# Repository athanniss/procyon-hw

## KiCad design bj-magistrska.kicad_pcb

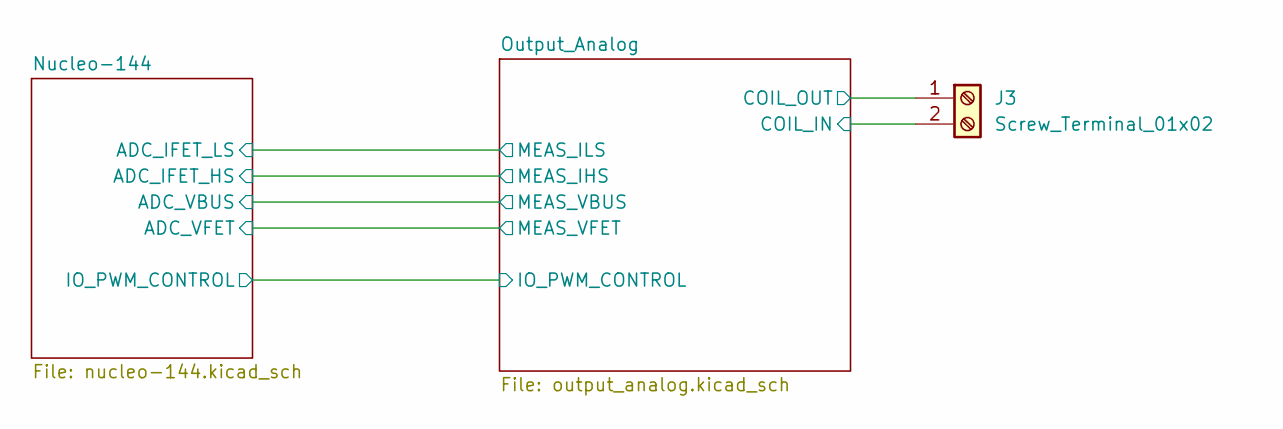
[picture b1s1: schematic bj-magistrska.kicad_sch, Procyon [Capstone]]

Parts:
J3: Screw_Terminal_01x02; TerminalBlock_Phoenix_MKDS-1,5-2-5.08_1x02_P5.08mm_Horizont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; Mfg. Part Number 1985904

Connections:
/Output_Analog/COIL_IN: J3.2; also elsewhere on the board
/Output_Analog/COIL_OUT: J3.1; also elsewhere on the board

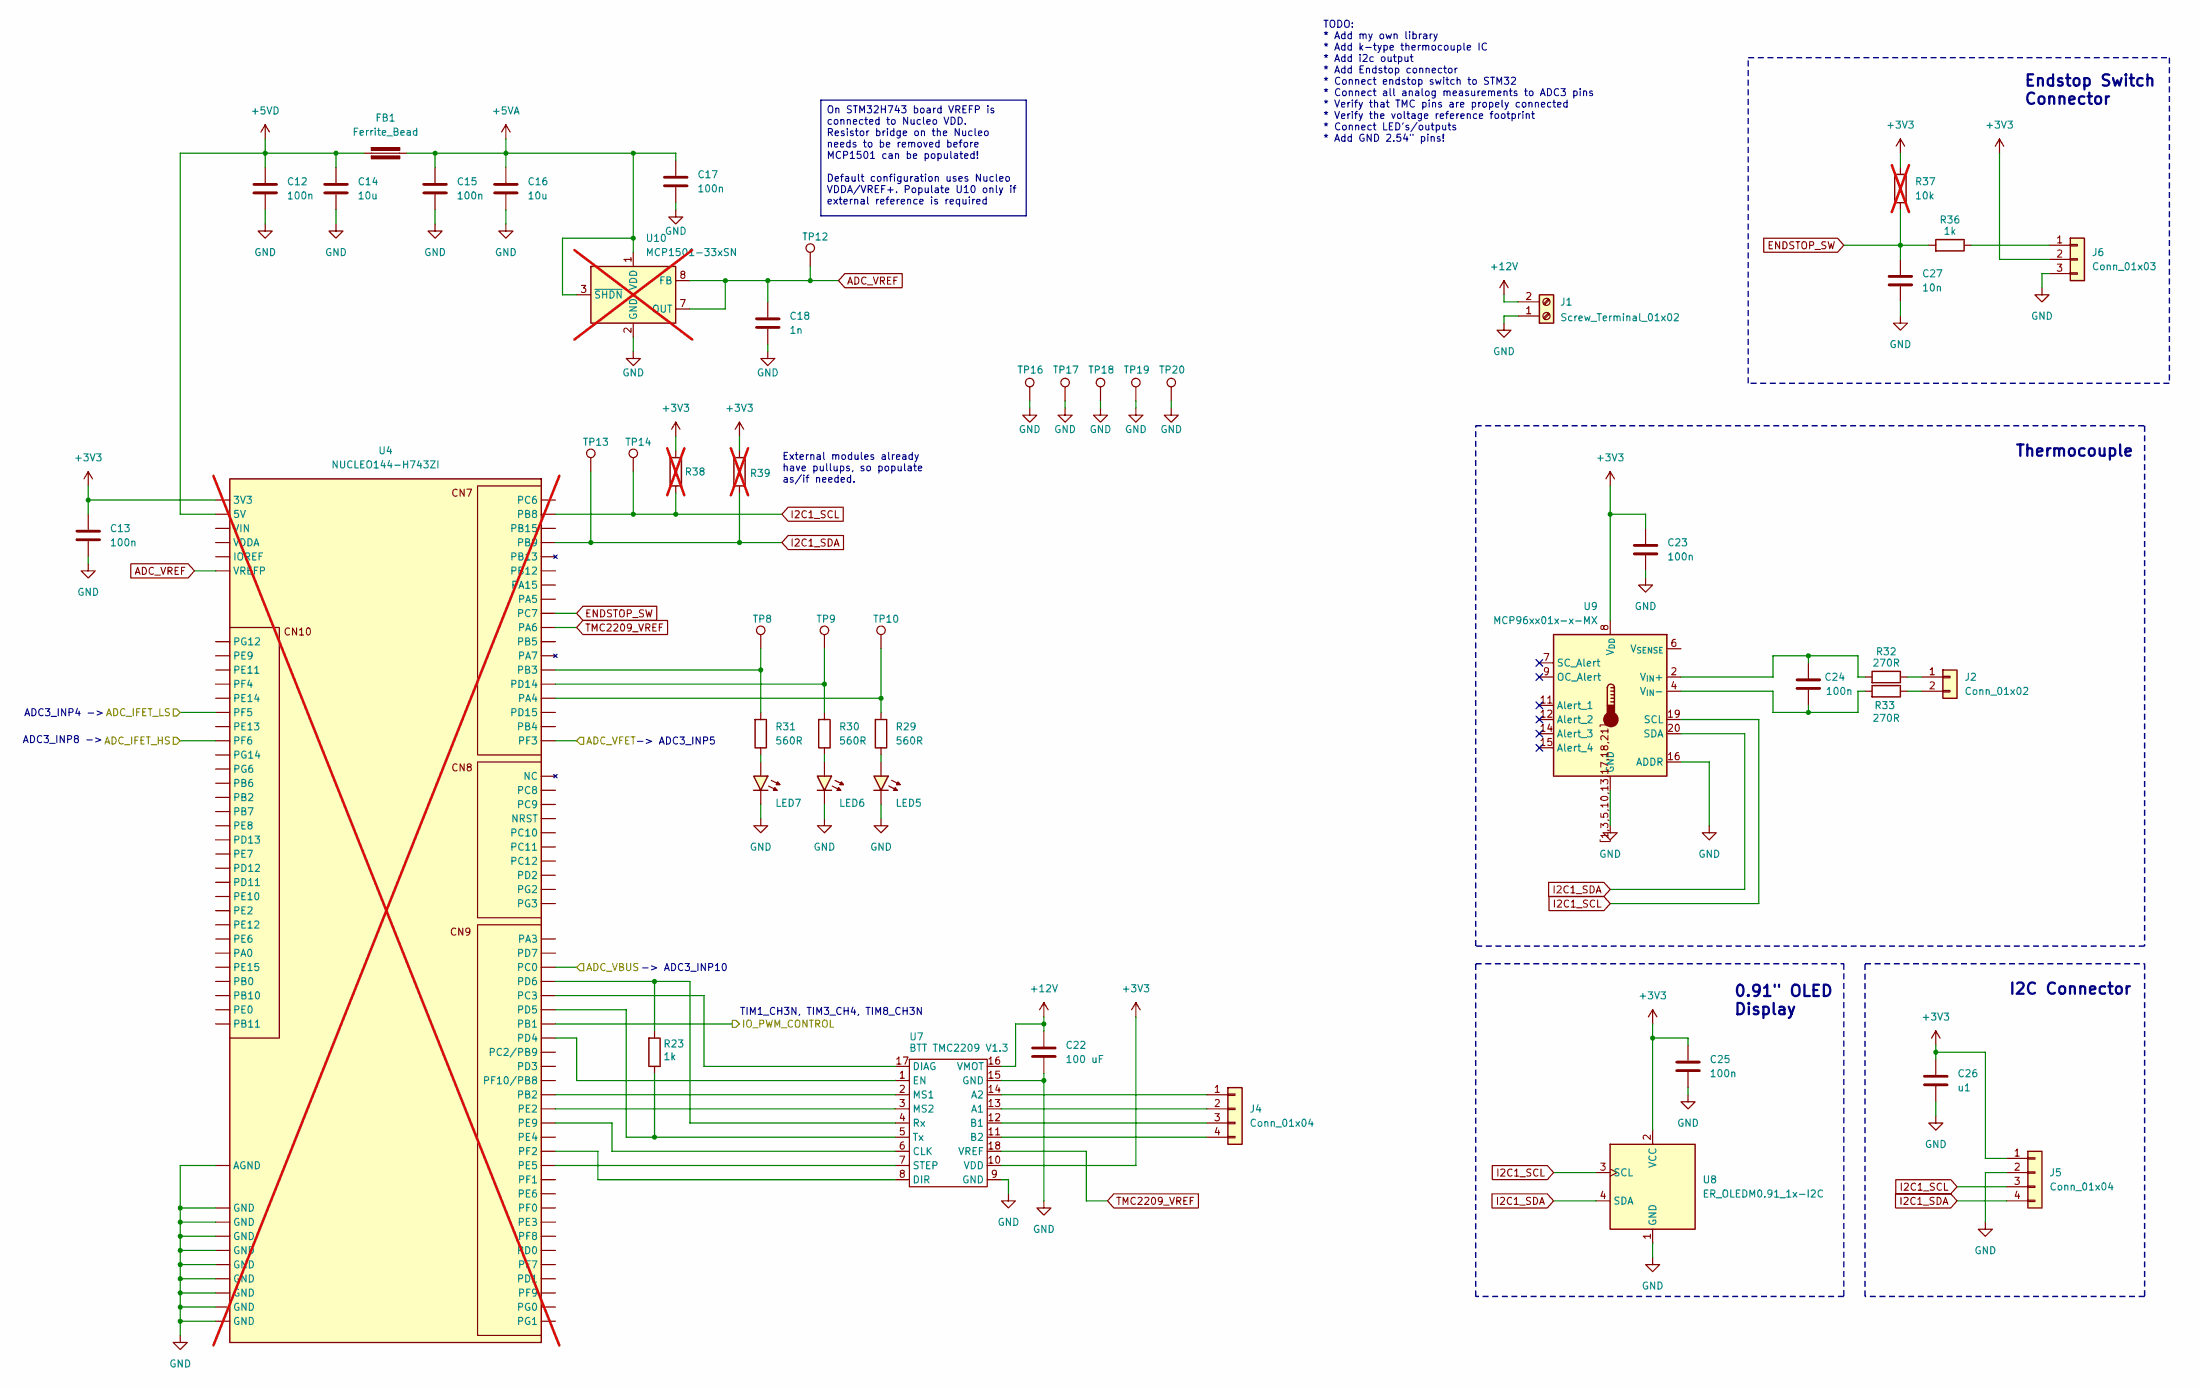
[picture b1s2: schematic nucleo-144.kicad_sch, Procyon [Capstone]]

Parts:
C12, C13, C15, C17, C23, C24, C25: 100n; C_0603_1608Metric
C14, C16: 10u; C_0805_2012Metric
C18: 1n; C_0603_1608Metric
C22: 100 uF; C_Elec_6.3x5.8
C26: u1; C_0603_1608Metric
C27: 10n; C_0603_1608Metric
FB1: Ferrite_Bead; Ferrite_0603_1608Metric
J1: Screw_Terminal_01x02; TerminalBlock_Phoenix_MKDS-1,5-2-5.08_1x02_P5.08mm_Horizont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; Mfg. Part Number 1985904
J2: Conn_01x02; JST_PH_S2B-PH-K_1x02_P2.00mm_Horizontal
J4, J5: Conn_01x04; JST_PH_S4B-PH-K_1x04_P2.00mm_Horizontal
J6: Conn_01x03; JST_PH_S3B-PH-K_1x03_P2.00mm_Horizontal
LED5, LED6, LED7: ORANGE; LED_0805_2012Metric
R23, R36: 1k; R_0603_1608Metric
R29, R30, R31: 560R; R_0603_1608Metric
R32, R33: 270R; R_0603_1608Metric
R37: 10k; R_0603_1608Metric; not fitted
R38, R39: R_0603_1608Metric; not fitted
TP8, TP9, TP10, TP16, TP17, TP18, TP19, TP20: TestPoint; PinHeader_1x01_P2.54mm_Vertical
TP12, TP13, TP14: TestPoint; PinHeader_1x01_P2.00mm_Vertical
U4: NUCLEO144-H743ZI; ST_Zio_Only_Connectors_144_STLink; not fitted
U7: BTT TMC2209 V1.3; BTT-TMC2209-V1.3_RAISED
U8: ER_OLEDM0.91_1x-I2C
U9: MCP96xx01x-x-MX; QFN-20-1EP_5x5mm_P0.65mm_EP3.35x3.35mm
U10: MCP1501-33xSN; SOIC-8_3.9x4.9mm_P1.27mm; not fitted

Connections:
+3V3: C13.1, C23.1, C25.1, C26.1, J5.1, J6.2, R37.1, R38.1, R39.1, U4.CN8_7 (3V3), U7.10 (VDD), U8.2 (VCC), U9.8 (V_{DD})
+5VA: C15.1, C16.1, C17.1, FB1.2, U10.1 (VDD), U10.3 (~SHDN); also elsewhere on the board
+5VD: C12.1, C14.1, FB1.1, U4.CN8_9 (5V); also elsewhere on the board
+12V: C22.1, J1.2, U7.16 (VMOT); also elsewhere on the board
/Nucleo-144/ADC_IFET_HS: U4.CN10_11 (PF6); also elsewhere on the board
/Nucleo-144/ADC_IFET_LS: U4.CN10_9 (PF5); also elsewhere on the board
/Nucleo-144/ADC_VBUS: U4.CN9_3 (PC0); also elsewhere on the board
/Nucleo-144/ADC_VFET: U4.CN7_20 (PF3); also elsewhere on the board
/Nucleo-144/IO_PWM_CONTROL: U4.CN9_7 (РВ1); also elsewhere on the board
ADC_VREF: C18.1, TP12.1 (1_1), U4.CN7_6 (VREFP), U10.7 (OUT), U10.8 (FB)
ENDSTOP_SW: C27.1, R36.1, R37.2, U4.CN7_11 (PC7)
GND: C12.2, C13.2, C14.2, C15.2, C16.2, C17.2, C18.2, C22.2, C23.2, C25.2, C26.2, C27.2, J1.1, J5.2, J6.3, LED5.1 (K), LED6.1 (K), LED7.1 (K), TP16.1 (1_1), TP17.1 (1_1), TP18.1 (1_1), TP19.1 (1_1), TP20.1 (1_1), U4.CN7_8 (GND), U4.CN8_11 (GND), U4.CN8_13 (GND), U4.CN9_12 (GND), U4.CN9_23 (GND), U4.CN10_3 (AGND), U4.CN10_5 (GND), U4.CN10_17 (GND), U4.CN10_22 (GND), U4.CN10_27 (GND), U7.9 (GND), U7.15 (GND), U8.1 (GND), U9.1 (GND), U9.3 (GND), U9.5 (GND), U9.10 (GND), U9.13 (GND), U9.16 (ADDR), U9.17 (GND), U9.18 (GND), U9.21 (GND), U9.[1,3,5,10,13,17,18,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 (GND), U10.2 (GND), U10.4 (GND), U10.5 (GND), U10.6 (GND); also elsewhere on the board
I2C1_SCL: J5.3, R38.2, TP14.1 (1_1), U4.CN7_2 (PB8), U8.3 (SCL), U9.19 (SCL)
I2C1_SDA: J5.4, R39.2, TP13.1 (1_1), U4.CN7_4 (PB9), U8.4 (SDA), U9.20 (SDA)
unnamed: J2.1, R32.2
unnamed: J2.2, R33.2
unnamed: J4.1, U7.14 (A2)
unnamed: J4.2, U7.13 (A1)
unnamed: J4.3, U7.12 (B1)
unnamed: J4.4, U7.11 (B2)
unnamed: J6.1, R36.2
unnamed: LED5.2 (A), R29.2
unnamed: LED6.2 (A), R30.2
unnamed: LED7.2 (A), R31.2
unnamed: R29.1, TP10.1 (1_1), U4.CN7_17 (PA4)
unnamed: R31.1, TP8.1 (1_1), U4.CN7_15 (PB3)
unnamed: U4.CN9_8 (PD4), U7.1 (EN)
unnamed: R23.2, U4.CN9_6 (PD5), U7.5 (Tx)
unnamed: R23.1, U4.CN9_4 (PD6), U7.4 (Rx)
unnamed: R30.1, TP9.1 (1_1), U4.CN7_16 (PD14)
unnamed: U4.CN9_14 (PE2), U7.3 (MS2)
unnamed: U4.CN9_17 (PF2), U7.8 (DIR)
unnamed: U4.CN9_18 (РЕ5), U7.7 (STEP)
unnamed: U4.CN9_15 (РЕ9), U7.6 (CLK)
unnamed: U4.CN9_5 (РСЗ), U7.17 (DIAG)
unnamed: U4.CN9_13 (РВ2), U7.2 (MS1)
unnamed: C24.1, R32.1, U9.2 (V_{IN}+)
unnamed: C24.2, R33.1, U9.4 (V_{IN}-)
TMC2209_VREF: U4.CN7_12 (PA6), U7.18 (VREF)

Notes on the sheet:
TIM1_CH3N, TIM3_CH4, TIM8_CH3N
Thermocouple
0.91" OLED Display
ADC3_INP4 ->
Endstop Switch Connector
ADC3_INP8 ->
External modules already have pullups, so populate as/if needed.
TODO: * Add my own library * Add k-type thermocouple IC * Add i2c output * Add Endstop connector * Connect endstop switch to STM32 * Connect all analog measurements to ADC3 pins * Verify that TMC pins are propely connected * Verify the voltage reference footprint * Connect LED's/outputs * Add GND 2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
-> ADC3_INP10
-> ADC3_INP5
I2C Connector
On STM32H743 board VREFP is connected to Nucleo VDD. Resistor bridge on the Nucleo needs to be removed before MCP1501 can be populated! Default configuration uses Nucleo VDDA/VREF+. Populate U10 only if external reference is required

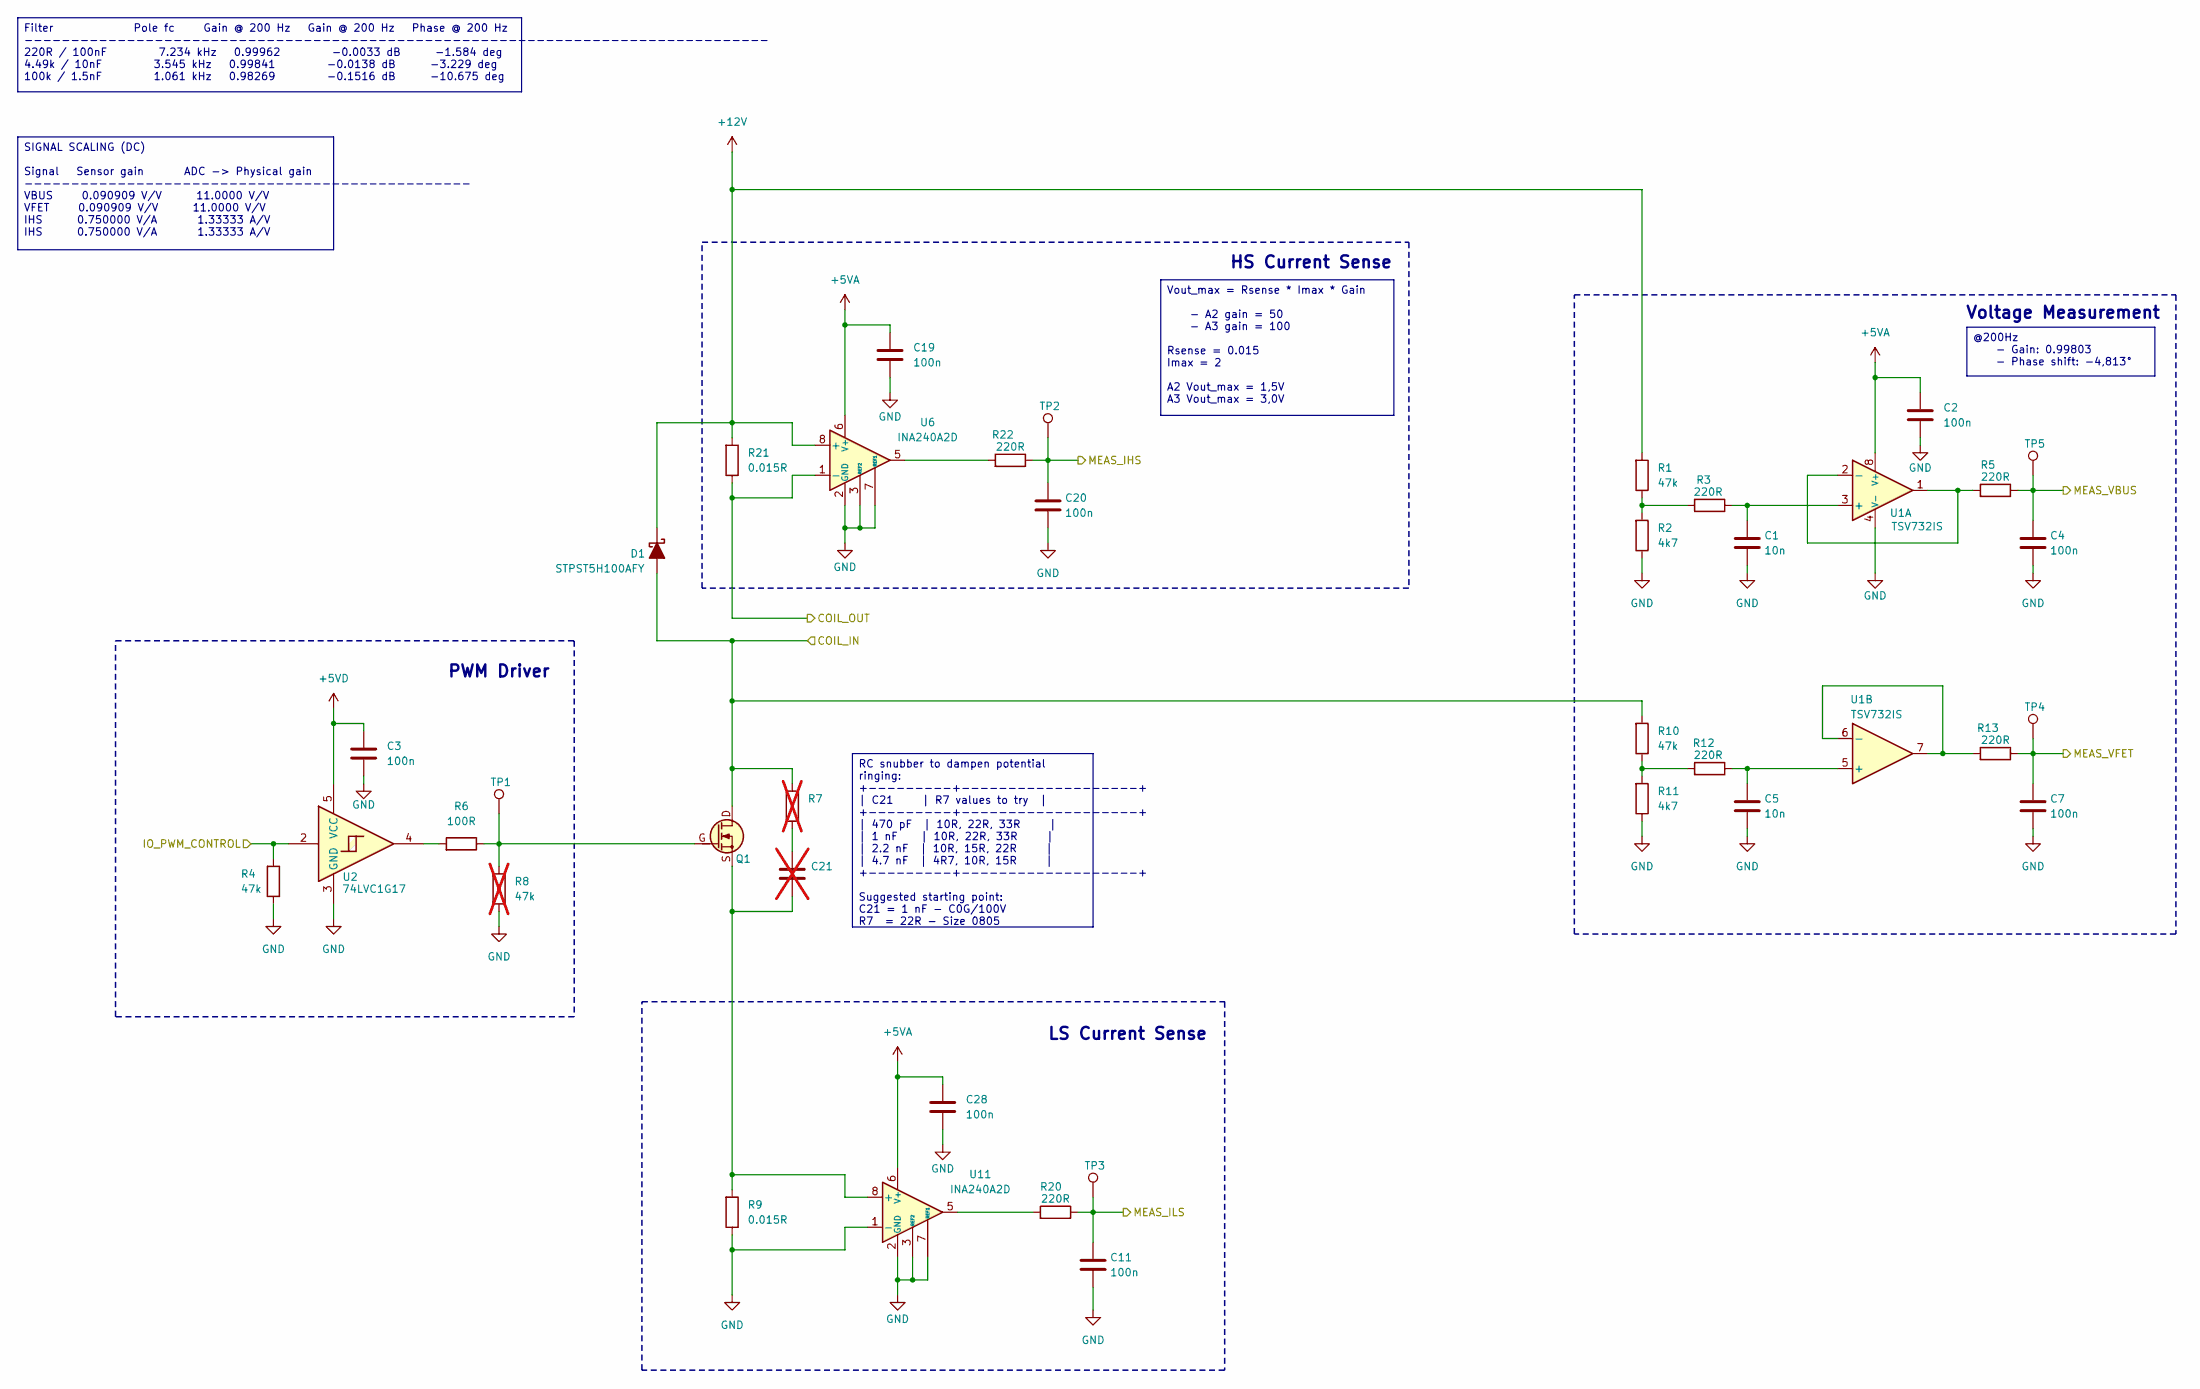
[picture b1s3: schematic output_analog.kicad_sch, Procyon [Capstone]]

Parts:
C1, C5: 10n; C_0603_1608Metric
C2, C3, C4, C7, C11, C19, C20, C28: 100n; C_0603_1608Metric
C21: C_0603_1608Metric; not fitted
D1: STPST5H100AFY; D_SOD-128; Mfg. Part Number STPST5H100AFY
Q1: DMTH10H009LPSQ-13; Diodes_PowerDI5060-8_ThermalVias; Mfg. Part Number DMTH10H009LPSQ-13
R1, R4, R10: 47k; R_0603_1608Metric
R2, R11: 4k7; R_0603_1608Metric
R3, R5, R12, R13, R20, R22: 220R; R_0603_1608Metric
R6: 100R; R_0603_1608Metric
R7: R_0805_2012Metric; not fitted
R8: 47k; R_0603_1608Metric; not fitted
R9, R21: 0.015R; R_1206_3216Metric; Mfg. Part Number MFSA1206R0150FCM
TP1, TP2, TP3, TP4, TP5: TestPoint; PinHeader_1x01_P2.00mm_Vertical
U1: TSV732IS; MSOP-8_3x3mm_P0.65mm; Mfg. Part Number TSV732IST
U2: 74LVC1G17; SOT-23-5; Mfg. Part Number SN74LVC1G17DBVR
U6, U11: INA240A2D; SOIC-8_3.9x4.9mm_P1.27mm

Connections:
+5VA: C2.1, C19.1, C28.1, U1.8 (V+), U6.6 (V+), U11.6 (V+); also elsewhere on the board
+5VD: C3.1, U2.5 (VCC); also elsewhere on the board
+12V: D1.1 (K), R1.1, R21.1, U6.8 (+); also elsewhere on the board
/Nucleo-144/ADC_IFET_HS: C20.1, R22.2, TP2.1 (1_1); also elsewhere on the board
/Nucleo-144/ADC_IFET_LS: C11.1, R20.2, TP3.1 (1_1); also elsewhere on the board
/Nucleo-144/ADC_VBUS: C4.1, R5.2, TP5.1 (1_1); also elsewhere on the board
/Nucleo-144/ADC_VFET: C7.1, R13.2, TP4.1 (1_1); also elsewhere on the board
/Nucleo-144/IO_PWM_CONTROL: R4.1, U2.2; also elsewhere on the board
/Output_Analog/COIL_IN: D1.2 (A), Q1.D, R7.1, R10.1; also elsewhere on the board
/Output_Analog/COIL_OUT: R21.2, U6.1 (-); also elsewhere on the board
GND: C1.2, C2.2, C3.2, C4.2, C5.2, C7.2, C11.2, C19.2, C20.2, C28.2, R2.2, R4.2, R8.1, R9.2, R11.2, U1.4 (V-), U2.3 (GND), U6.2 (GND), U6.3 (REF2), U6.4 (GND), U6.7 (REF1), U11.1 (-), U11.2 (GND), U11.3 (REF2), U11.4 (GND), U11.7 (REF1); also elsewhere on the board
unnamed: C21.1, R7.2
unnamed: Q1.G, R6.2, R8.2, TP1.1 (1_1)
unnamed: R1.2, R2.1, R3.1
unnamed: R6.1, U2.4
unnamed: R10.2, R11.1, R12.1
unnamed: R20.1, U11.5
unnamed: R22.1, U6.5
unnamed: C1.1, R3.2, U1.3 (+)
unnamed: R5.1, U1.1, U1.2 (-)
unnamed: C5.1, R12.2, U1.5 (+)
unnamed: R13.1, U1.6 (-), U1.7
unnamed: C21.2, Q1.S, R9.1, U11.8 (+)

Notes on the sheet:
LS Current Sense
Voltage Measurement
PWM Driver
HS Current Sense
RC snubber to dampen potential ringing: +---------+-------------------+ | C21 | R7 values to try | +---------+-------------------+ | 470 pF | 10R, 22R, 33R | | 1 nF | 10R, 22R, 33R | | 2.2 nF | 10R, 15R, 22R | | 4.7 nF | 4R7, 10R, 15R | +---------+-------------------+ Suggested starting point: C21 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
Vout_max = Rsense * Imax * Gain - A2 gain = 50 - A3 gain = 100 Rsense = 0.015 Imax = 2 A2 Vout_max = 1,5V A3 Vout_max = 3,0V
Filter Pole fc Gain @ 200 Hz Gain @ 200 Hz Phase @ 200 Hz -------------------------------------------------------------------------------- 220R / 100nF 7.234 kHz 0.99962 -0.0033 dB -1.584 deg 4.49k / 10nF 3.545 kHz 0.99841 -0.0138 dB -3.229 deg 100k / 1.5nF 1.061 kHz 0.98269 -0.1516 dB -10.675 deg
SIGNAL SCALING (DC) Signal Sensor gain ADC -> Physical gain ------------------------------------------------ VBUS 0.090909 V/V 11.0000 V/V VFET 0.090909 V/V 11.0000 V/V IHS 0.750000 V/A 1.33333 A/V IHS 0.750000 V/A 1.33333 A/V
@200Hz - Gain: 0.99803 - Phase shift: -4,813°

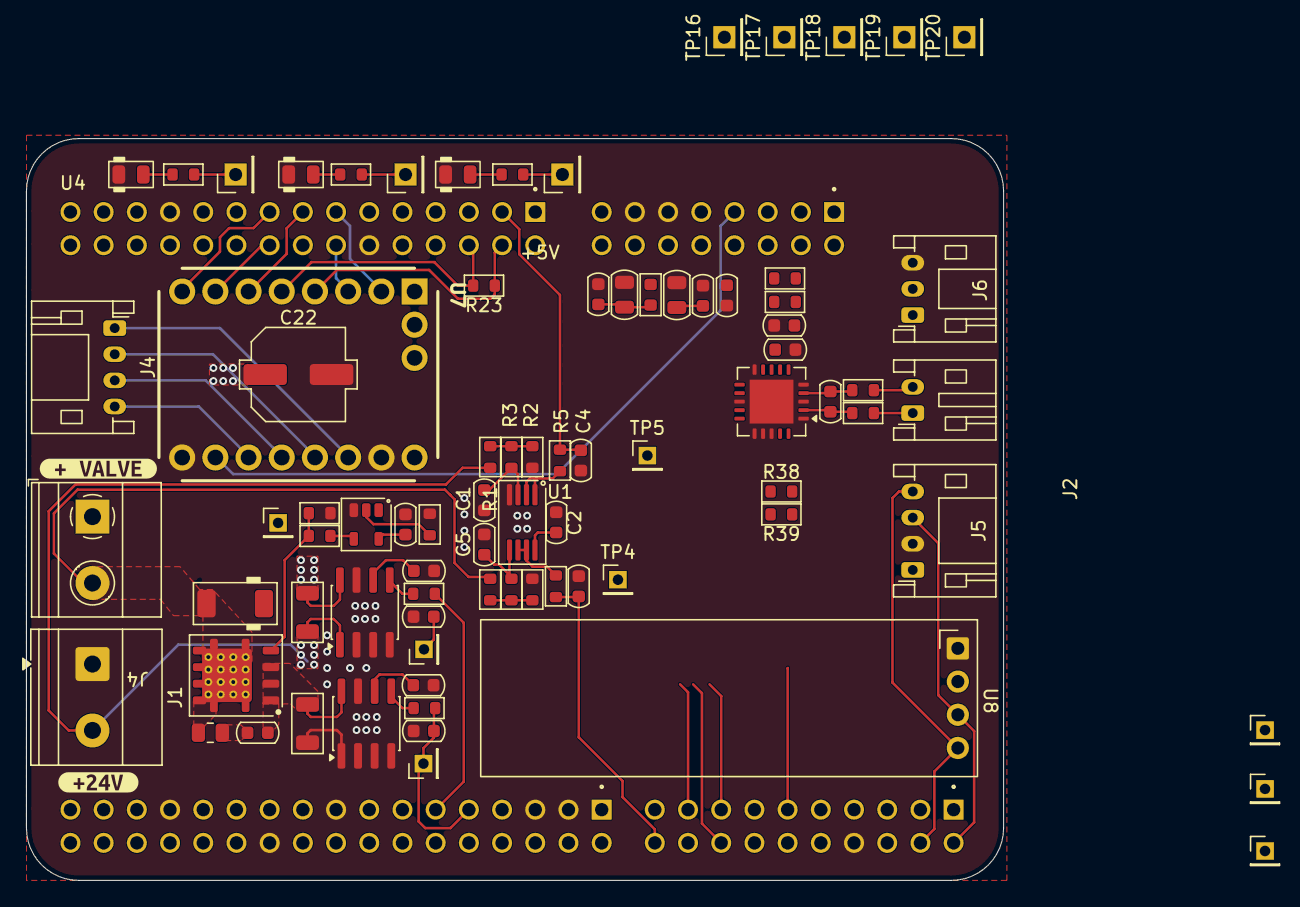
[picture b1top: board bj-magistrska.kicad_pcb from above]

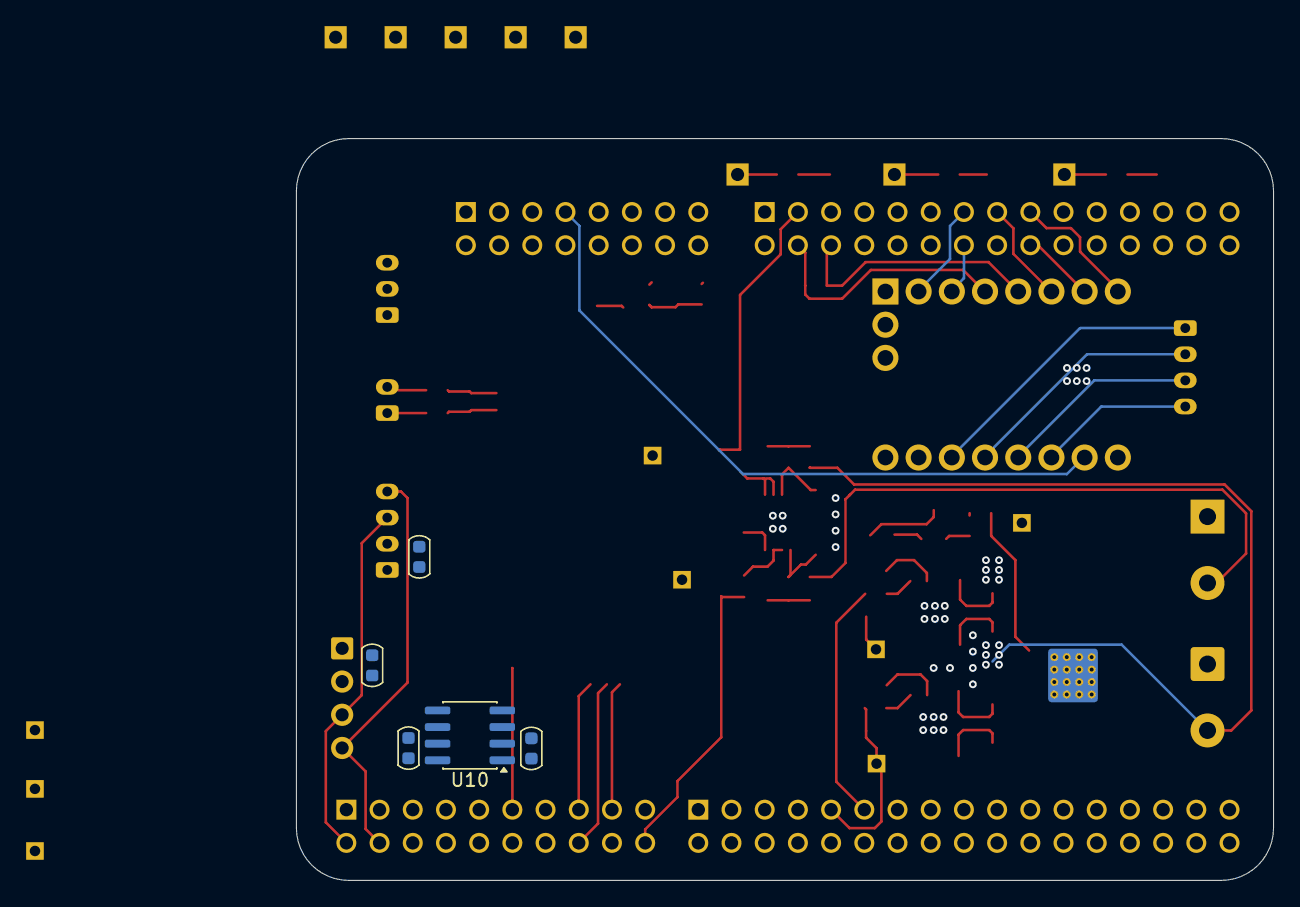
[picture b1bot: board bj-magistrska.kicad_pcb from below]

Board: 4 copper layers, 74.8 x 56.7 mm, 89 parts (5 on the bottom side), 53 nets.

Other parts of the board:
kibuzzard-66E6F4D2: G***; kibuzzard-66E6F4D2
kibuzzard-66E6F4F3: G***; kibuzzard-66E6F4F3

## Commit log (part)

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2025-02-18 - Removed I2C lines - Added mission resistor between buffer and transistor gate - Removed wetting current & high range enable - Added ILI9341 TFT LCD - Removed OLED - Upped current gain to ~100
2025-02-18 JINX V2.0
